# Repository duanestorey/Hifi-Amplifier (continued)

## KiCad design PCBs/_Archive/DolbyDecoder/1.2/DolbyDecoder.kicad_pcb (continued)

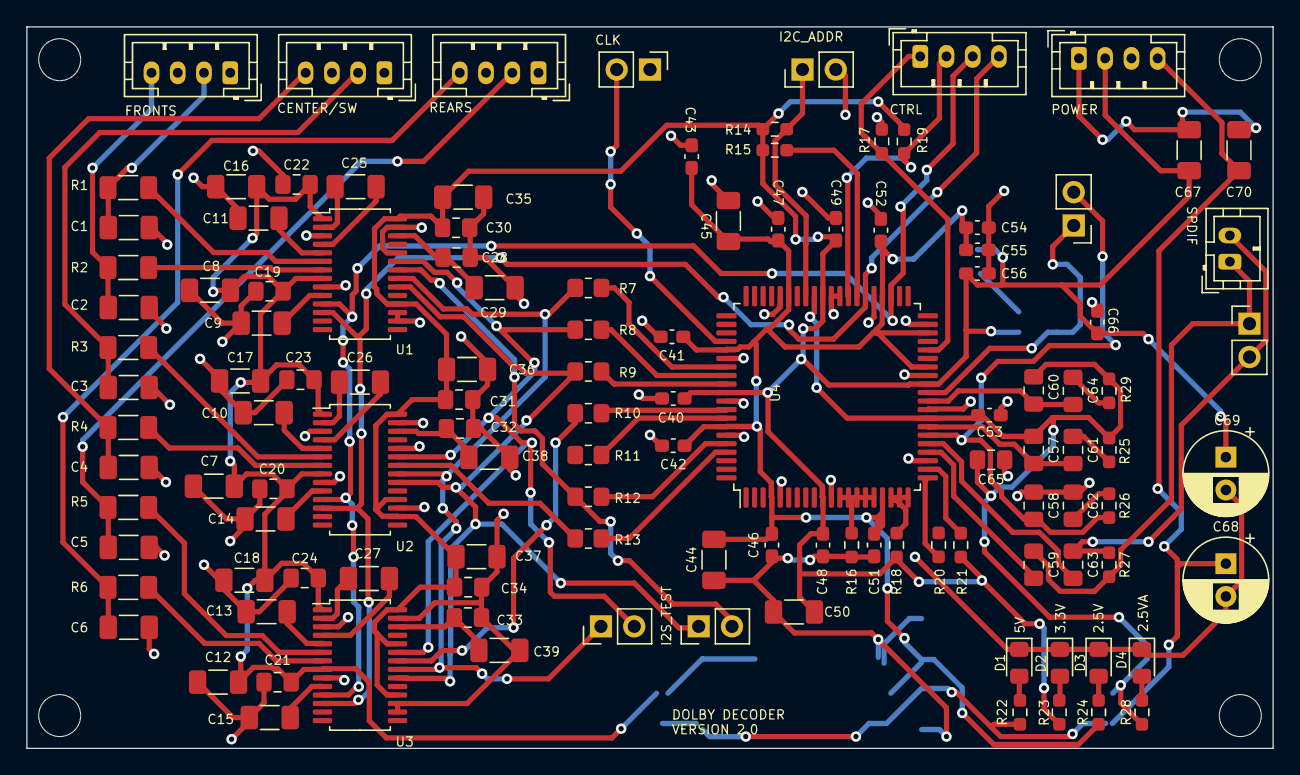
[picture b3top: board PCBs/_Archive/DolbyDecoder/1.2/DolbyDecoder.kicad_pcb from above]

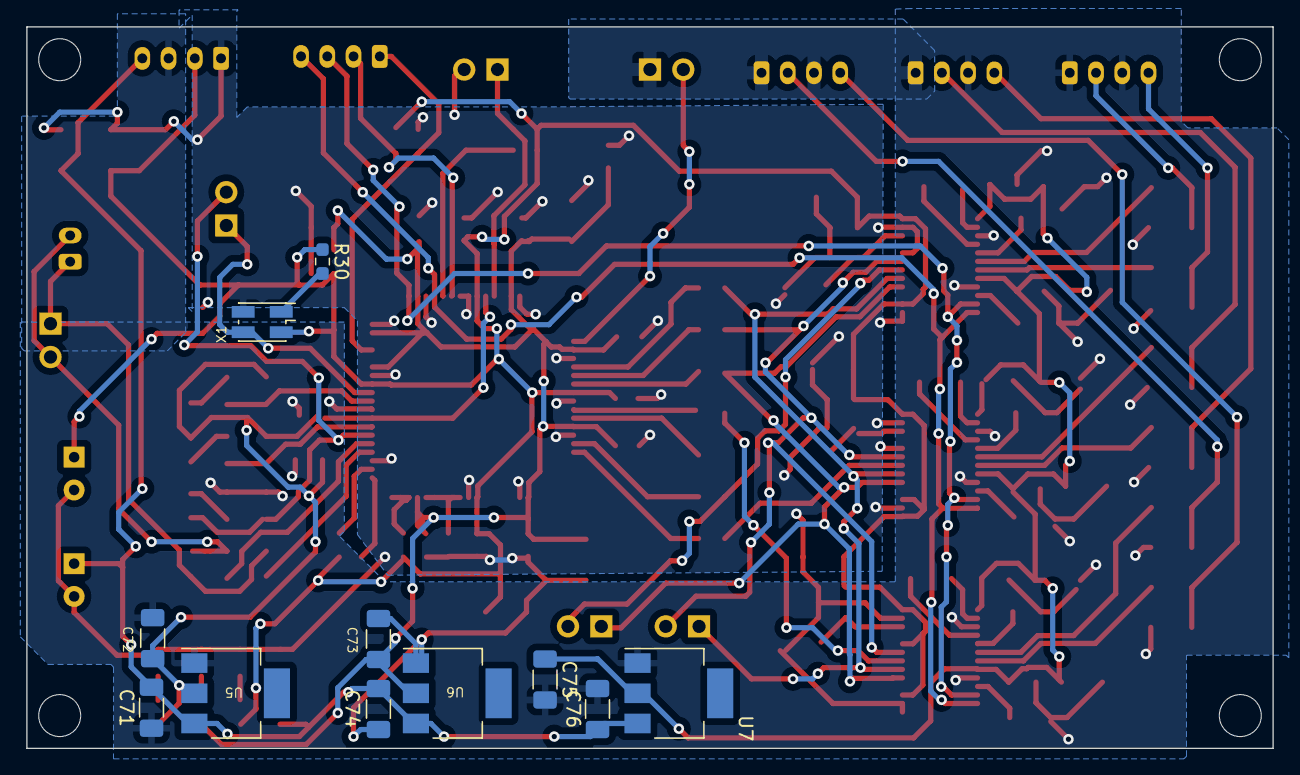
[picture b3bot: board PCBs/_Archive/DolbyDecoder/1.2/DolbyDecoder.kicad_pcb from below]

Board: 2 copper layers, 95.0 x 55.0 mm, 134 parts (11 on the bottom side), 74 nets.

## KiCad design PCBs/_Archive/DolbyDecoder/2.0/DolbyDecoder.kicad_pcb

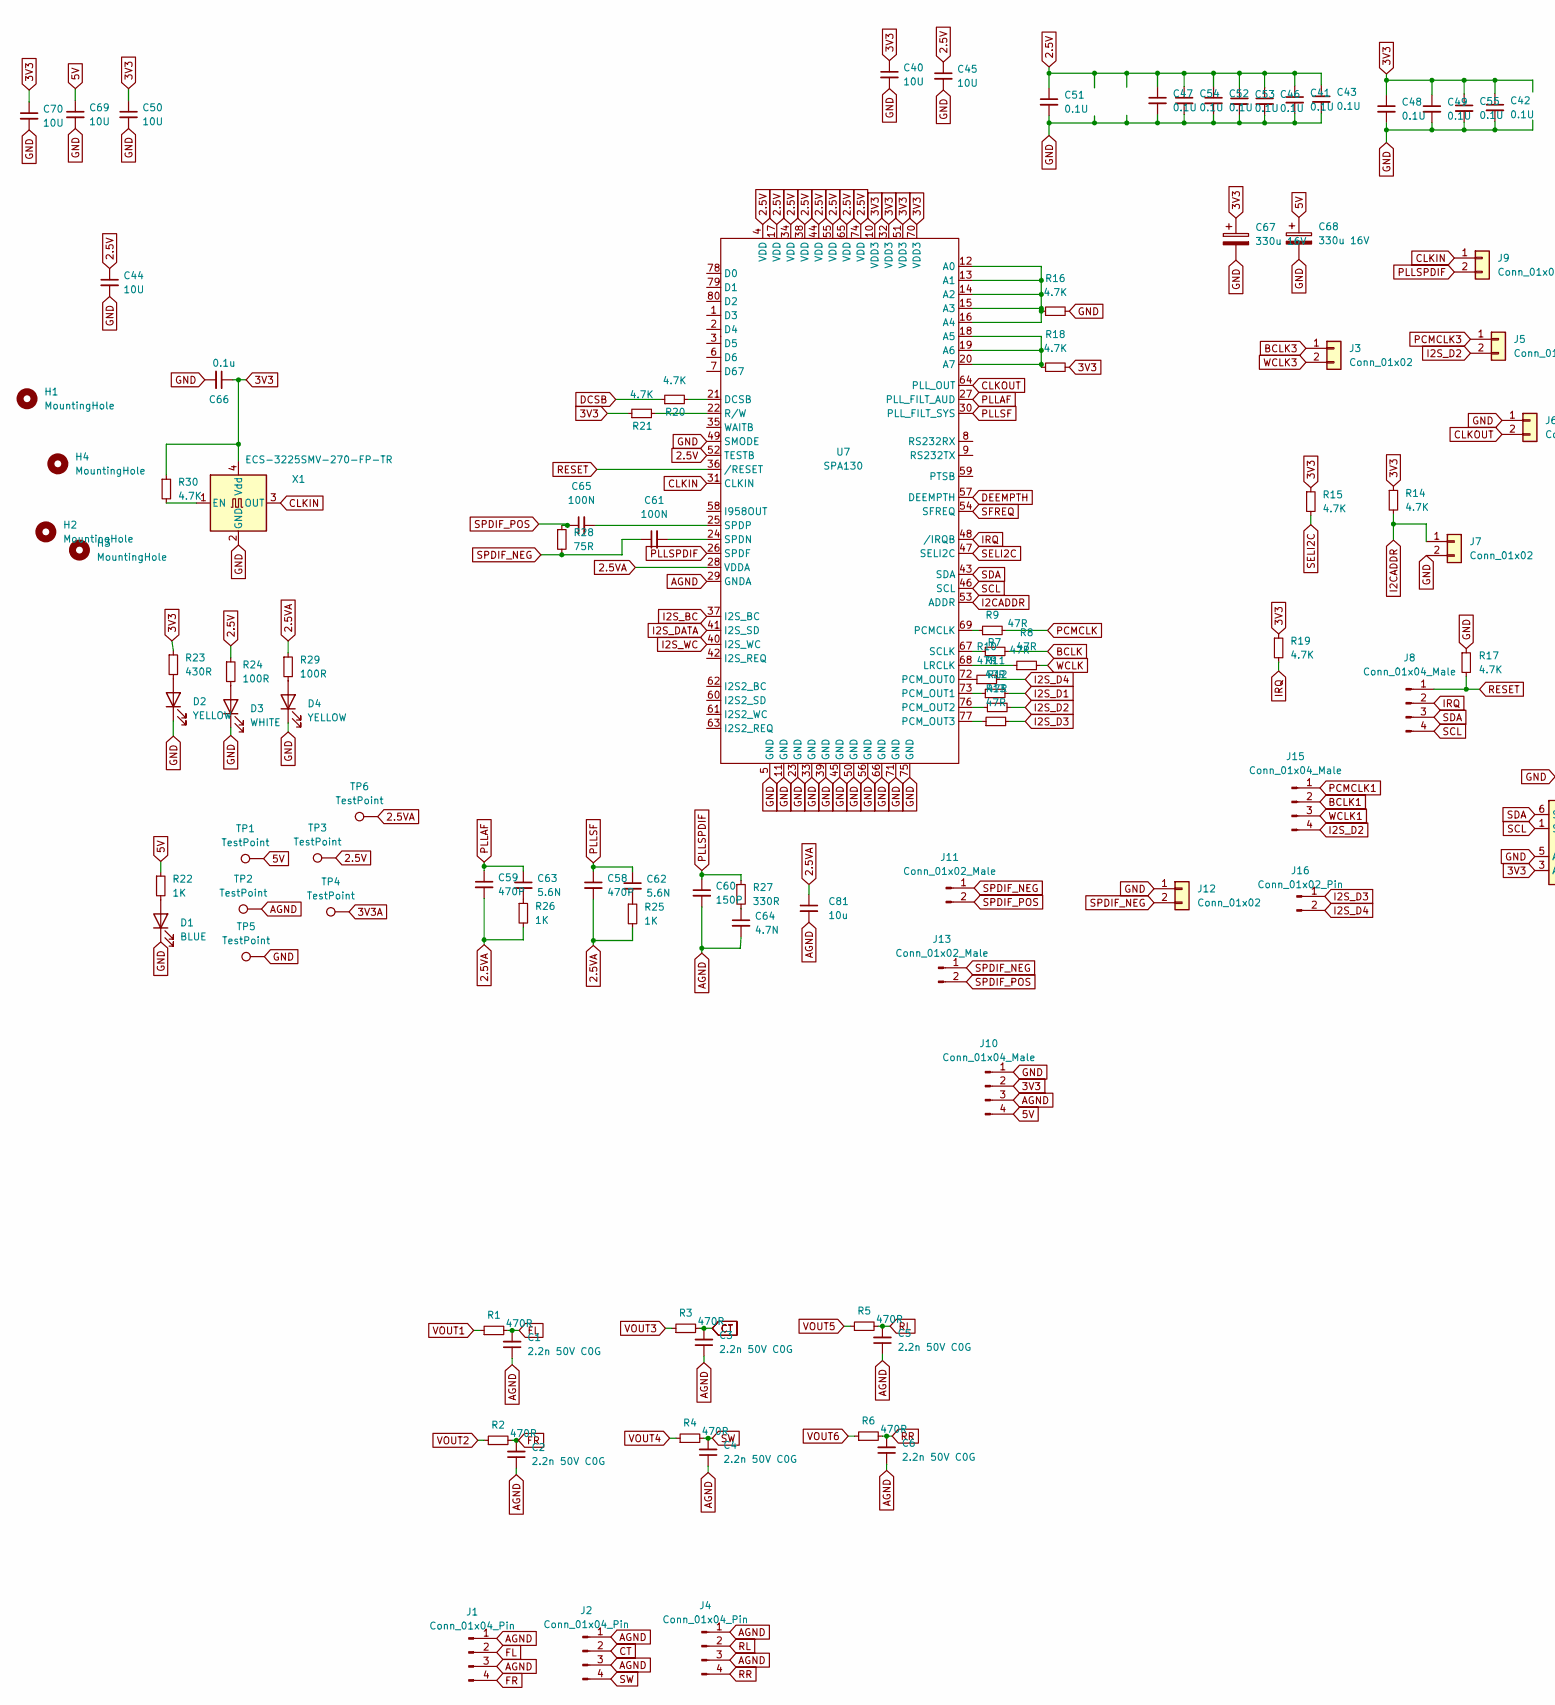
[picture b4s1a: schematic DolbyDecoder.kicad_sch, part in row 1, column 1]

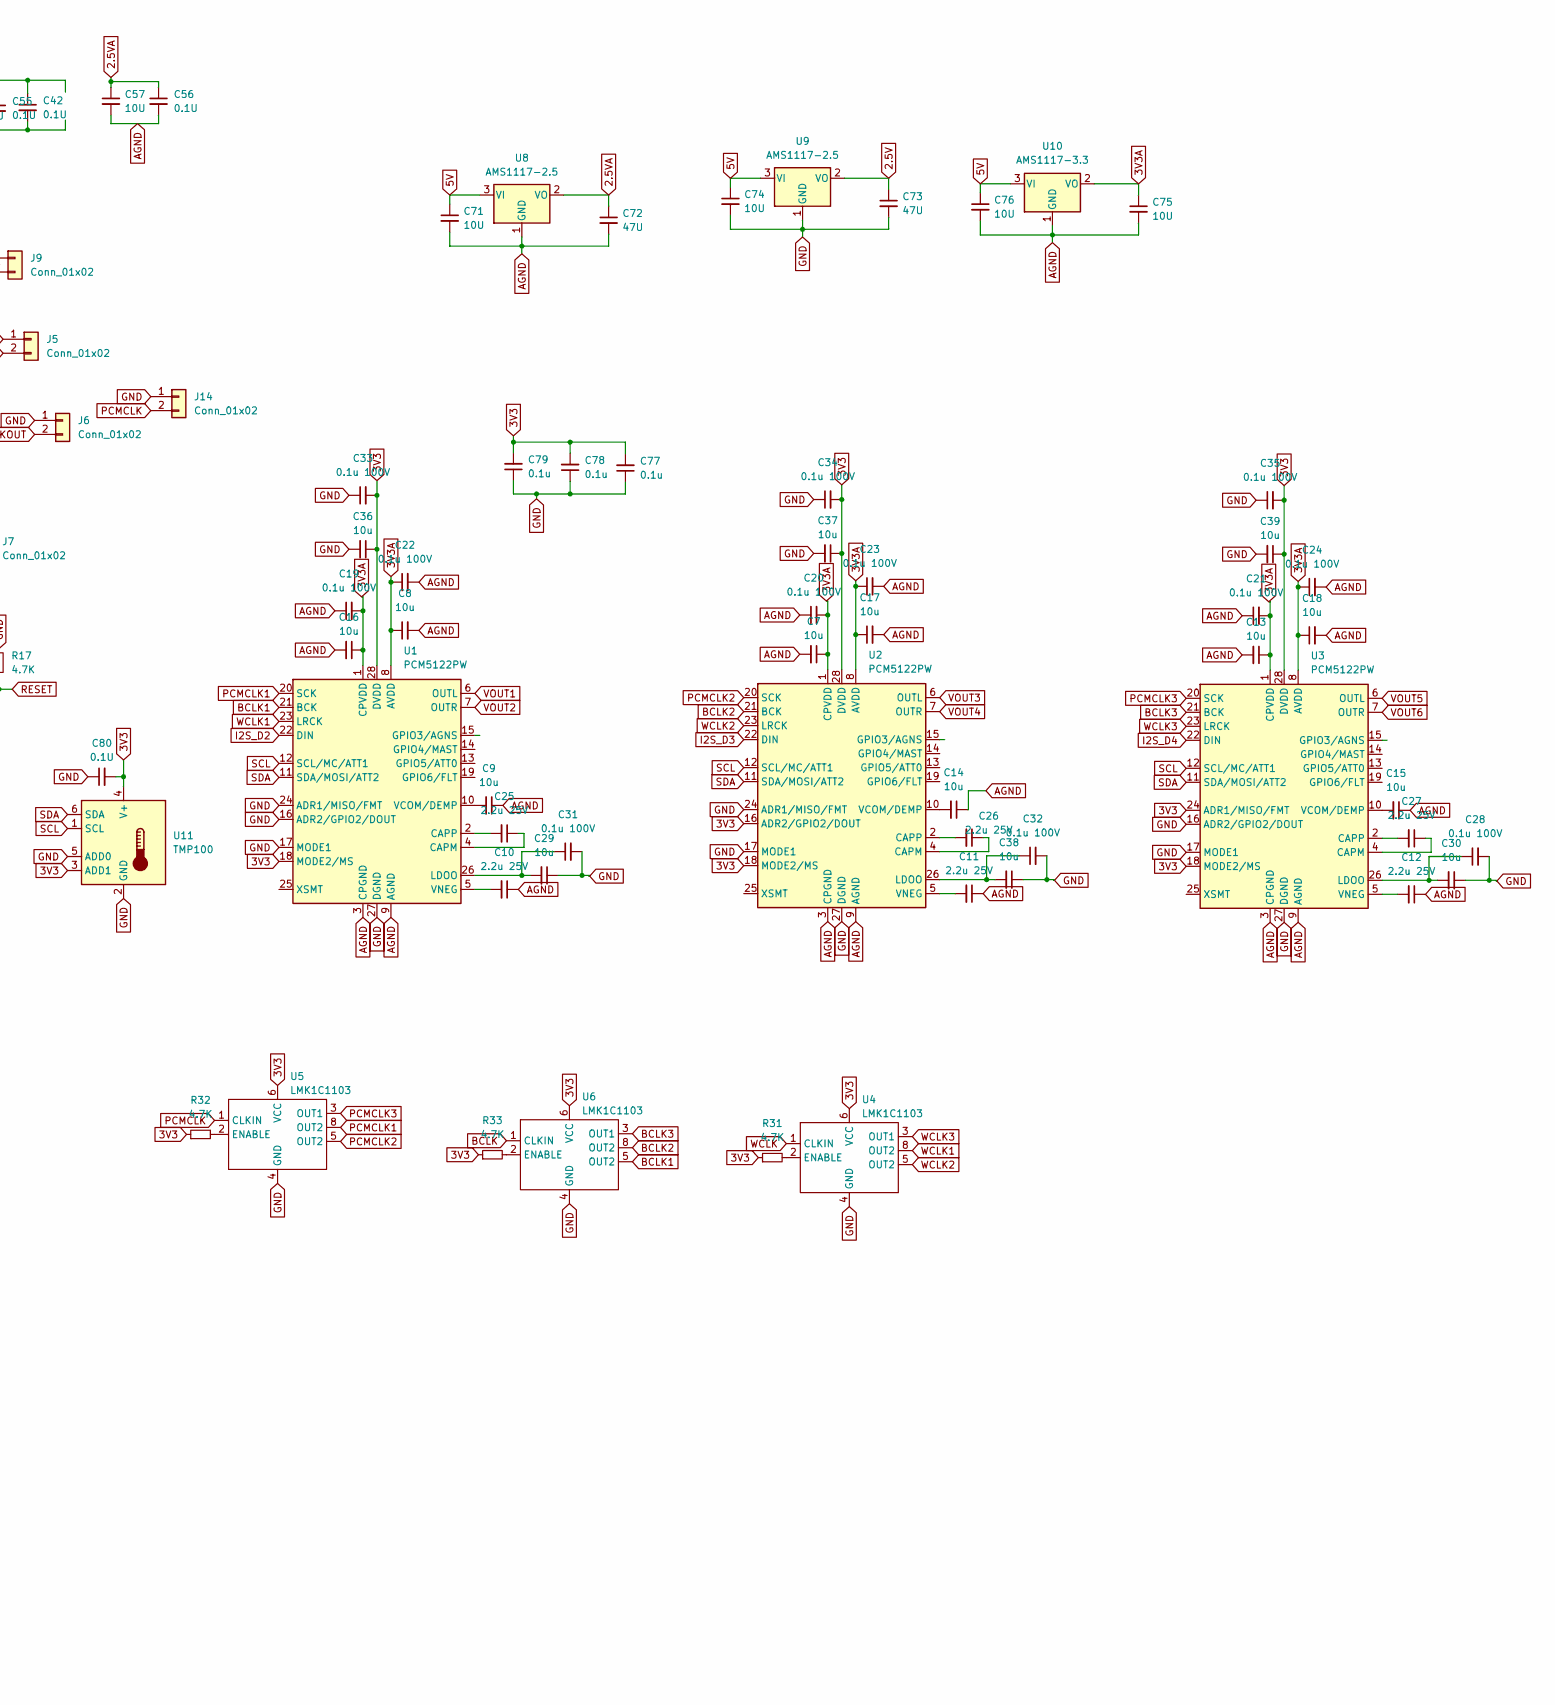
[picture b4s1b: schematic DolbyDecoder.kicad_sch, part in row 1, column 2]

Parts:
C1, C2, C3, C4, C5, C6: 2.2n 50V C0G; C_1206_3216Metric_Pad1.33x1.80mm_HandSolder
C7, C8, C9, C13, C14, C15, C16, C17, C18, C29, C30, C36, C37, C38, C39, C81: 10u; C_1206_3216Metric_Pad1.33x1.80mm_HandSolder
C10, C11, C12, C25, C26, C27: 2.2u 25V; C_1206_3216Metric_Pad1.33x1.80mm_HandSolder
C19, C20, C21, C22, C23, C24, C28, C31, C32, C33, C34, C35: 0.1u 100V; C_0805_2012Metric_Pad1.18x1.45mm_HandSolder
C40, C44, C45, C50, C69, C70, C71, C74, C75, C76: 10U; C_1206_3216Metric_Pad1.33x1.80mm_HandSolder
C41, C42, C43, C46, C47, C48, C49, C51, C52, C53, C54, C55, C56, C80: 0.1U; C_0805_2012Metric_Pad1.18x1.45mm_HandSolder
C57: 10U; C_0805_2012Metric_Pad1.18x1.45mm_HandSolder
C58, C59: 470P; C_0805_2012Metric_Pad1.18x1.45mm_HandSolder
C60: 150P; C_0805_2012Metric_Pad1.18x1.45mm_HandSolder
C61, C65: 100N; C_0805_2012Metric_Pad1.18x1.45mm_HandSolder
C62, C63: 5.6N; C_0805_2012Metric_Pad1.18x1.45mm_HandSolder
C64: 4.7N; C_0805_2012Metric_Pad1.18x1.45mm_HandSolder
C66, C77, C78, C79: 0.1u; C_0805_2012Metric_Pad1.18x1.45mm_HandSolder
C67, C68: 330u 16V; CP_Radial_D8.0mm_P2.50mm
C72, C73: 47U; C_1206_3216Metric_Pad1.33x1.80mm_HandSolder
D1: BLUE; LED_0805_2012Metric_Pad1.15x1.40mm_HandSolder
D2, D4: YELLOW; LED_0805_2012Metric_Pad1.15x1.40mm_HandSolder
D3: WHITE; LED_0805_2012Metric_Pad1.15x1.40mm_HandSolder
H1, H2, H3, H4: MountingHole; MountingHole_3.2mm_M3
J1, J2, J4: Conn_01x04_Pin; JST_PH_B4B-PH-K_1x04_P2.00mm_Vertical
J3, J5, J6, J7, J9, J12, J14: Conn_01x02; PinHeader_1x02_P2.54mm_Vertical
J8: Conn_01x04_Male; JST_PH_B4B-PH-K_1x04_P2.00mm_Vertical
J10: Conn_01x04_Male; JST_XH_B4B-XH-A_1x04_P2.50mm_Vertical
J11: Conn_01x02_Male; JST_XH_B2B-XH-A_1x02_P2.50mm_Vertical
J13: Conn_01x02_Male; PinHeader_1x02_P2.54mm_Vertical
J15: Conn_01x04_Male; PinHeader_1x04_P2.54mm_Vertical
J16: Conn_01x02_Pin; PinHeader_1x02_P2.54mm_Vertical
R1, R2, R3, R4, R5, R6: 470R; R_1206_3216Metric_Pad1.30x1.75mm_HandSolder
R7, R8, R9, R10, R11, R12, R13: 47R; R_0805_2012Metric_Pad1.20x1.40mm_HandSolder
R14, R15, R16, R17, R18, R19, R20, R21, R30, R31, R32, R33: 4.7K; R_0603_1608Metric_Pad0.98x0.95mm_HandSolder
R22, R25, R26: 1K; R_0603_1608Metric_Pad0.98x0.95mm_HandSolder
R23: 430R; R_0603_1608Metric_Pad0.98x0.95mm_HandSolder
R24, R29: 100R; R_0603_1608Metric_Pad0.98x0.95mm_HandSolder
R27: 330R; R_0603_1608Metric_Pad0.98x0.95mm_HandSolder
R28: 75R; R_0603_1608Metric_Pad0.98x0.95mm_HandSolder
TP1, TP2, TP3, TP4, TP5, TP6: TestPoint; TestPoint_THTPad_1.5x1.5mm_Drill0.7mm
U1, U2, U3: PCM5122PW; TSSOP-28_4.4x9.7mm_P0.65mm
U4, U5, U6: LMK1C1103; TSSOP-8_4.4x3mm_P0.65mm
U7: SPA130; LQFP-80_14x14mm_P0.65mm
U8, U9: AMS1117-2.5; SOT-223
U10: AMS1117-3.3; SOT-223
U11: TMP100; SOT-23-6
X1: ECS-3225SMV-270-FP-TR; Oscillator_SMD_EuroQuartz_XO32-4Pin_3.2x2.5mm_HandSoldering

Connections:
2.5V: C41.1, C43.1, C44.1, C45.1, C46.1, C47.1, C51.1, C52.1, C53.1, C54.1, C73.1, R24.1, TP3.1, U7.4 (VDD), U7.17 (VDD), U7.34 (VDD), U7.38 (VDD), U7.44 (VDD), U7.52 (TESTB), U7.55 (VDD), U7.65 (VDD), U7.74 (VDD), U9.2 (VO)
2.5VA: C56.1, C57.1, C58.2, C59.2, C72.1, C81.1, R25.2, R26.2, R29.1, TP6.1, U7.28 (VDDA), U8.2 (VO)
3V3: C33.2, C34.2, C35.2, C36.1, C37.1, C39.1, C40.1, C42.1, C48.1, C49.1, C50.1, C55.1, C66.1, C67.1, C70.1, C77.2, C78.2, C79.2, C80.2, J10.2, R14.1, R15.1, R18.2, R19.1, R21.1, R23.1, R30.1, R31.1, R32.1, R33.1, U1.18 (MODE2/MS), U1.28 (DVDD), U2.16 (ADR2/GPIO2/DOUT), U2.18 (MODE2/MS), U2.28 (DVDD), U3.18 (MODE2/MS), U3.24 (ADR1/MISO/FMT), U3.28 (DVDD), U4.6 (VCC), U5.6 (VCC), U6.6 (VCC), U7.10 (VDD3), U7.32 (VDD3), U7.51 (VDD3), U7.70 (VDD3), U11.3 (ADD1), U11.4 (V+), X1.4 (Vdd)
3V3A: C7.1, C8.1, C13.1, C16.1, C17.1, C18.1, C19.2, C20.2, C21.2, C22.1, C23.1, C24.1, C75.1, TP4.1, U1.1 (CPVDD), U1.8 (AVDD), U2.1 (CPVDD), U2.8 (AVDD), U3.1 (CPVDD), U3.8 (AVDD), U10.2 (VO)
5V: C68.1, C69.1, C71.1, C74.1, C76.1, J10.4, R22.1, TP1.1, U8.3 (VI), U9.3 (VI), U10.3 (VI)
AGND: C1.1, C2.1, C3.1, C4.1, C5.1, C6.1, C7.2, C8.2, C9.1, C10.1, C11.1, C12.1, C13.2, C14.1, C15.1, C16.2, C17.2, C18.2, C19.1, C20.1, C21.1, C22.2, C23.2, C24.2, C56.2, C57.2, C60.2, C64.2, C71.2, C72.2, C75.2, C76.2, C81.2, J1.1, J1.3, J2.1, J2.3, J4.1, J4.3, J10.3, TP2.1, U1.3 (CPGND), U1.9 (AGND), U2.3 (CPGND), U2.9 (AGND), U3.3 (CPGND), U3.9 (AGND), U7.29 (GNDA), U8.1 (GND), U10.1 (GND)
BCLK: R7.2, U6.1 (CLKIN)
BCLK1: J15.2, U1.21 (BCK), U6.5 (OUT2)
BCLK2: U2.21 (BCK), U6.8 (OUT2)
BCLK3: J3.1, U3.21 (BCK), U6.3 (OUT1)
CLKIN: J9.1, U7.31 (CLKIN), X1.3 (OUT)
CLKOUT: J6.2, U7.64 (PLL_OUT)
CT: C3.2, J2.2, R3.2
DCSB: R20.1
DEEMPTH: U7.57 (DEEMPTH)
FL: C1.2, J1.2, R1.2
FR: C2.2, J1.4, R2.2
GND: C28.2, C29.1, C30.1, C31.2, C32.2, C33.1, C34.1, C35.1, C36.2, C37.2, C38.1, C39.2, C40.2, C41.2, C42.2, C43.2, C44.2, C45.2, C46.2, C47.2, C48.2, C49.2, C50.2, C51.2, C52.2, C53.2, C54.2, C55.2, C66.2, C67.2, C68.2, C69.2, C70.2, C73.2, C74.2, C77.1, C78.1, C79.1, C80.1, D1.1 (K), D2.1 (K), D3.1 (K), D4.1 (K), J6.1, J7.2, J10.1, J12.1, J14.1, R16.2, R17.1, TP5.1, U1.16 (ADR2/GPIO2/DOUT), U1.17 (MODE1), U1.24 (ADR1/MISO/FMT), U1.27 (DGND), U2.17 (MODE1), U2.24 (ADR1/MISO/FMT), U2.27 (DGND), U3.16 (ADR2/GPIO2/DOUT), U3.17 (MODE1), U3.27 (DGND), U4.4 (GND), U5.4 (GND), U6.4 (GND), U7.5 (GND), U7.11 (GND), U7.23 (GND), U7.33 (GND), U7.39 (GND), U7.45 (GND), U7.49 (SMODE), U7.50 (GND), U7.56 (GND), U7.66 (GND), U7.71 (GND), U7.75 (GND), U9.1 (GND), U11.2 (GND), U11.5 (ADD0), X1.2 (GND)
I2CADDR: J7.1, R14.2, U7.53 (ADDR)
I2S_BC: U7.37 (I2S_BC)
I2S_D1: R11.2
I2S_D2: J5.2, J15.4, R12.2, U1.22 (DIN)
I2S_D3: J16.1, R13.2, U2.22 (DIN)
I2S_D4: J16.2, R10.2, U3.22 (DIN)
I2S_DATA: U7.41 (I2S_SD)
I2S_WC: U7.40 (I2S_WC)
IRQ: J8.2, R19.2, U7.48 (/IRQB)
unnamed: C62.2, R25.1
unnamed: C63.2, R26.1
unnamed: C64.1, R27.2
unnamed: D1.2 (A), R22.2
unnamed: D2.2 (A), R23.2
unnamed: D3.2 (A), R24.2
unnamed: D4.2 (A), R29.2
unnamed: C25.1, U1.4 (CAPM)
unnamed: C25.2, U1.2 (CAPP)
unnamed: C29.2, C31.1, U1.26 (LDOO)
unnamed: C9.2, U1.10 (VCOM/DEMP)
unnamed: C10.2, U1.5 (VNEG)
unnamed: C26.1, U2.4 (CAPM)
unnamed: C26.2, U2.2 (CAPP)
unnamed: C32.1, C38.2, U2.26 (LDOO)
unnamed: C14.2, U2.10 (VCOM/DEMP)
unnamed: C11.2, U2.5 (VNEG)
unnamed: C27.1, U3.4 (CAPM)
unnamed: C27.2, U3.2 (CAPP)
unnamed: C28.1, C30.2, U3.26 (LDOO)
unnamed: C15.2, U3.10 (VCOM/DEMP)
unnamed: C12.2, U3.5 (VNEG)
unnamed: R31.2, U4.2 (ENABLE)
unnamed: R32.2, U5.2 (ENABLE)
unnamed: R33.2, U6.2 (ENABLE)
unnamed: R16.1, U7.12 (A0), U7.13 (A1), U7.14 (A2), U7.15 (A3), U7.16 (A4)
unnamed: R18.1, U7.18 (A5), U7.19 (A6), U7.20 (A7)
unnamed: R20.2, U7.21 (DCSB)
unnamed: R8.1, U7.68 (LRCLK)
unnamed: R9.1, U7.69 (PCMCLK)
unnamed: R10.1, U7.72 (PCM_OUT0)
unnamed: R11.1, U7.73 (PCM_OUT1)
unnamed: R12.1, U7.76 (PCM_OUT2)
unnamed: R13.1, U7.77 (PCM_OUT3)
unnamed: R21.2, U7.22 (R/W)
unnamed: R7.1, U7.67 (SCLK)
unnamed: C61.2, U7.24 (SPDN)
unnamed: C65.2, U7.25 (SPDP)
unnamed: R30.2, X1.1 (EN)
PCMCLK: J14.2, R9.2, U5.1 (CLKIN)
PCMCLK1: J15.1, U1.20 (SCK), U5.8 (OUT2)
PCMCLK2: U2.20 (SCK), U5.5 (OUT2)
PCMCLK3: J5.1, U3.20 (SCK), U5.3 (OUT1)
PLLAF: C59.1, C63.1, U7.27 (PLL_FILT_AUD)
PLLSF: C58.1, C62.1, U7.30 (PLL_FILT_SYS)
PLLSPDIF: C60.1, J9.2, R27.1, U7.26 (SPDF)
RESET: J8.1, R17.2, U7.36 (/RESET)
RL: C5.2, J4.2, R5.2
RR: C6.2, J4.4, R6.2
SCL: J8.4, U1.12 (SCL/MC/ATT1), U2.12 (SCL/MC/ATT1), U3.12 (SCL/MC/ATT1), U7.46 (SCL), U11.1 (SCL)
SDA: J8.3, U1.11 (SDA/MOSI/ATT2), U2.11 (SDA/MOSI/ATT2), U3.11 (SDA/MOSI/ATT2), U7.43 (SDA), U11.6 (SDA)
SELI2C: R15.2, U7.47 (SELI2C)
SFREQ: U7.54 (SFREQ)
SPDIF_NEG: C61.1, J11.1, J12.2, J13.1, R28.2
SPDIF_POS: C65.1, J11.2, J13.2, R28.1
SW: C4.2, J2.4, R4.2
VOUT1: R1.1, U1.6 (OUTL)
VOUT2: R2.1, U1.7 (OUTR)
VOUT3: R3.1, U2.6 (OUTL)
VOUT4: R4.1, U2.7 (OUTR)
VOUT5: R5.1, U3.6 (OUTL)
VOUT6: R6.1, U3.7 (OUTR)
WCLK: R8.2, U4.1 (CLKIN)
WCLK1: J15.3, U1.23 (LRCK), U4.8 (OUT2)
WCLK2: U2.23 (LRCK), U4.5 (OUT2)
WCLK3: J3.2, U3.23 (LRCK), U4.3 (OUT1)

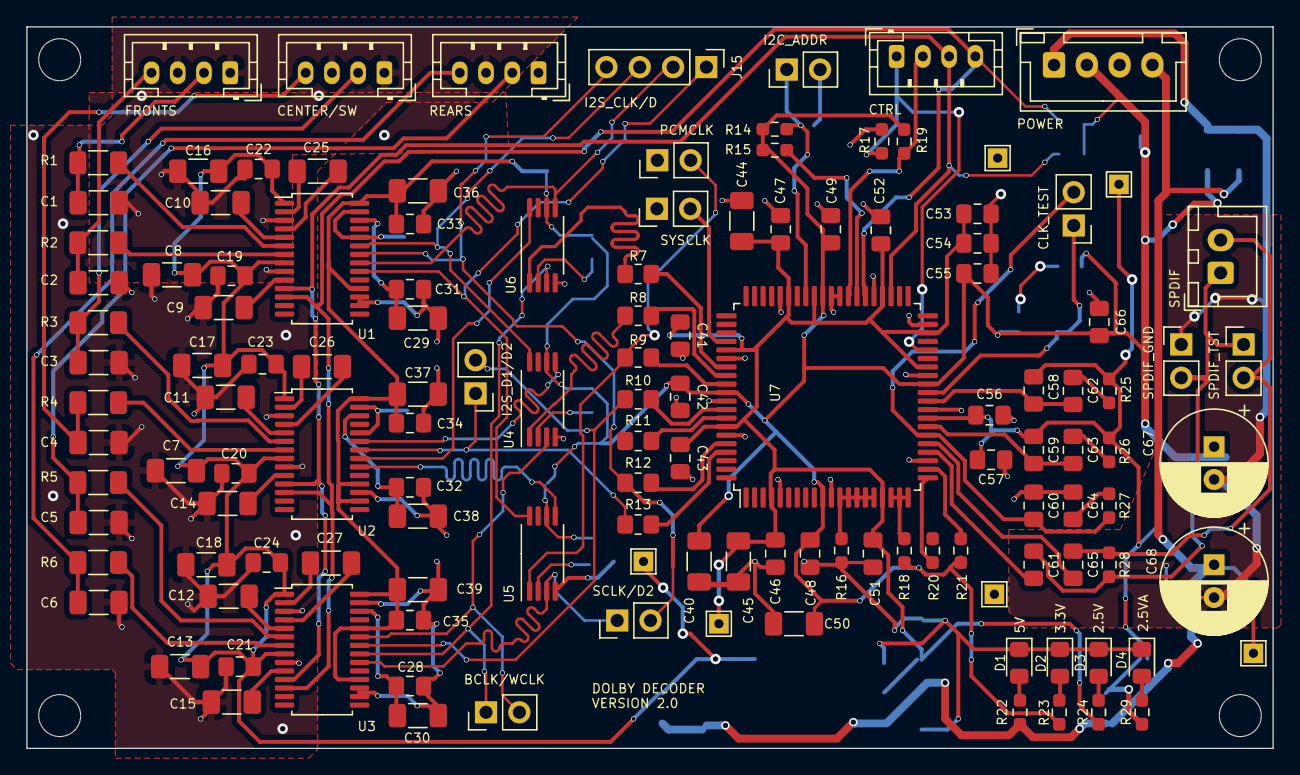
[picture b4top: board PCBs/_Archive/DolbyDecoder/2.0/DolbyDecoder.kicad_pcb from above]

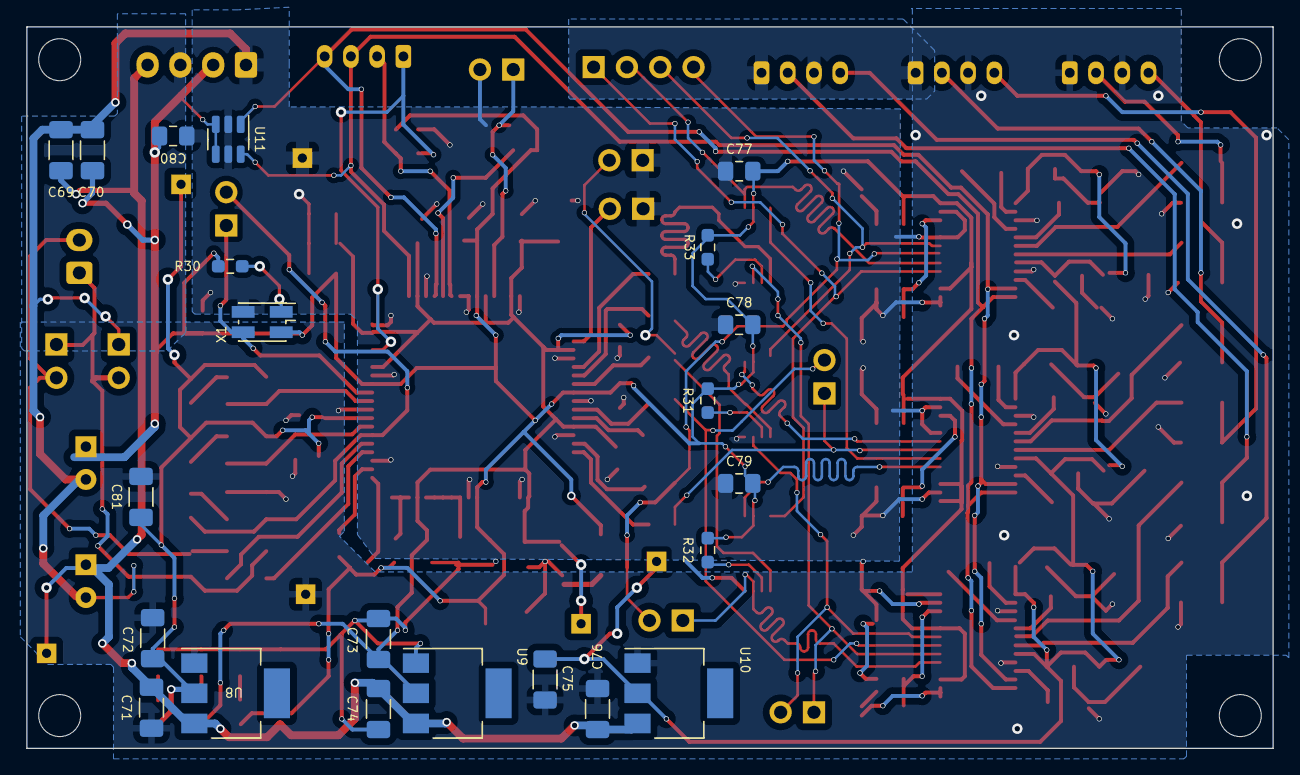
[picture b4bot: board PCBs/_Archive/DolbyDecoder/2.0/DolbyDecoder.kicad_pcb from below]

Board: 2 copper layers, 95.0 x 55.0 mm, 156 parts (22 on the bottom side), 86 nets.

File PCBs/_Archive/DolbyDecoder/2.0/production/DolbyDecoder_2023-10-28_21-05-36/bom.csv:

Designator,Footprint,Quantity,Value,LCSC Part #
"C1, C2, C3, C4, C5, C6",1206,6,2.2n 50V C0G,
"C10, C11, C12, C25, C26, C27",1206,6,2.2u 25V,
"C13, C14, C15, C16, C17, C18, C29, C30, C36, C37, C38, C39, C43, C44, C45, C50, C67, C7, C70, C71, C74, C75, C76, C8, C9",1206,25,10u,
"C19, C20, C21, C22, C23, C24, C28, C31, C32, C33, C34, C35",0805,12,0.1u 100V,
"C40, C41, C42, C46, C47, C48, C49, C51, C52, C53, C55, C56, C57, C77, C78, C79",0805,16,0.1U,
C54,0805,1,10U,
"C58, C59",0805,2,470P,
C60,0805,1,150P,
"C61, C65",0805,2,100N,
"C62, C63",0805,2,5.6N,
C64,0805,1,4.7N,
C66,0603,1,100N,
"C68, C69",CP_Radial_D8.0mm_P2.50mm,2,330u 16V,
"C72, C73",1206,2,47U,
D1,0805,1,BLUE,
"D2, D4",0805,2,YELLOW,
D3,0805,1,WHITE,
"H1, H2, H3, H4",MountingHole_3.2mm_M3,4,MountingHole,
"J1, J2, J3",JST_PH_B4B-PH-K_1x04_P2.00mm_Vertical,3,Conn_01x04_Pin,
J10,JST_XH_B4B-XH-A_1x04_P2.50mm_Vertical,1,Conn_01x04_Male,
J11,JST_XH_B2B-XH-A_1x02_P2.50mm_Vertical,1,Conn_01x02_Male,
J12,PinHeader_1x02_P2.54mm_Vertical,1,Conn_01x02_Male,
"J13, J4, J5, J6, J7, J9",PinHeader_1x02_P2.54mm_Vertical,6,Conn_01x02,
J8,JST_PH_B4B-PH-K_1x04_P2.00mm_Vertical,1,Conn_01x04_Male,
"R1, R2, R3, R4, R5, R6",1206,6,470R,
"R10, R11, R12, R13, R7, R8, R9",0805,7,47R,
"R14, R15, R16, R17, R18, R19, R20, R21, R30, R31, R32, R33",0603,12,4.7K,
"R22, R25, R26",0603,3,1K,
R23,0603,1,430R,
"R24, R29",0603,2,100R,
R27,0603,1,330R,
R28,0603,1,75R,
"U1, U2, U3",TSSOP-28_4.4x9.7mm_P0.65mm,3,PCM5122PW,
U10,SOT-223,1,AMS1117-3.3,
"U4, U5, U6",TSSOP-8_4.4x3mm_P0.65mm,3,LMK1C1103,
U7,LQFP-80_14x14mm_P0.65mm,1,SPA130,
"U8, U9",SOT-223,2,AMS1117-2.5,
X1,Oscillator_SMD_EuroQuartz_XO32-4Pin_3.2x2.5mm_HandSoldering,1,ECS-3225SMV-270-FP-TR,
